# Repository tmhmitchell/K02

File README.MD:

**Less, but better.** - Dieter Rams

After seeing the [Ferris Sweep](https://github.com/davidphilipbarr/Sweep) for the first time I've fallen in love, but as a designer I cannot accept the things the way they are. So I've done some experimentation with it.

I changed the overall form of the board so it can be a little bit more compact and be a canvas for expression in the matter of case design

This is a parcial redesign of the [Ferris Sweep 2 half-swept](https://github.com/davidphilipbarr/Sweep). In other words this is a:

- 34 keys.
- Diodeless.
- Low profile.
- Non-hotswap.
- Reversible PCB.
- Column staggered.
- [Tenting puck](https://splitkb.com/products/tenting-puck) compatible.
- Wireless and wired capable.
- Choc MBK spaced (17,5mm x 16,5mm).
- Cheaper than the [cheapino](https://github.com/tompi/cheapino) (at the time of the build).

### What have been done:

- Change PCB overall form.
- Add support screw holes.
- Add teardrop on solder joints.
- Reposition of the reset and power switch.
- Do an extensive and compreensive [assembly manual](/other/manuals/k02-assembly-manual.pdf).
- Create an alternative version with `USB-C` instead of `TRRS`.
- Add commissioned art by the brazilian artist [Aline Dal Pont](https://www.instagram.com/manifesto.efemero/).
- Remove all the informative silk graphics for a better looking board.

### What I may do<sup>1</sup>:

- Change the `USB-C` location.
- Make it compatible with choc V2 switches.
- Change the `USB-C` connector to mid-mount 6p.
- Design some _minimalist_ and _low profile_ cases.
- Create an 36 keys pcb with breakpoints/mousebites.
- Add a variation with choc spacing for [CFX keycaps](https://kbd.news/CFX-keycap-1553.html) (16,5mm x 16,5mm).

> <sup>1</sup> The main reason for not doing this at the moment is the lack of financial motivation. As I have to pay for every prototype and take time off to do the development and iterations I have to be mindful of the tasks I take. If you want to help [contact me](https://www.reddit.com/user/kynikoi_/) :)

## Versions

At the moment this repo contains 2 versions, one with `TRRS` and one with `USB-C` connecting the halves. The `TRRS` connector are objectively worse than the `USB-C` for this use case, due to it introducing a risk of short in the case that the halves are unpluged with the board powered on. On the other side, the `USB-C` if not wired correctly may introduce a [risk of being connected directly to a power supply](https://docs.qmk.fm/features/split_keyboard) by mistake. I've done the bare minimum to prevent it, I wired the `GND` and `VCC` trying to follow the USB protocol. Another problem with the `USB-C` is that this implementation doesn't follow the USB protocol, it just hijack some of the data pins.

The [gerber files are in the release section.](https://github.com/anothermimich/K02/releases)
The list of materials for each version are inside of the respective folder, [USB-C](/USB-C/README.MD) and [TRRS](/TRRS/README.MD).

## Assembly

As the pcb doesn't have any information guiding the assembly, I have done an [manual with visual instructions](/other/manuals/k02-assembly-manual.pdf).

## Keymap

I'm using the [Miryoku ZMK](https://github.com/manna-harbour/miryoku_zmk) keymap made by [Manna Harbour](https://github.com/manna-harbour). Bellow you can see the layout that I ended up<sup>2</sup>, if you want to replicate it you can use [compiled firmware](/other/keymaps/) or compile it from scratch with this [github workflow](https://github.com/anothermimich/miryoku_zmk/blob/master/.github/workflows/workflow-build-k02.yml), [custom_config.h](https://github.com/anothermimich/miryoku_zmk/blob/master/miryoku/custom_config.h), [cradio_left.conf](https://github.com/anothermimich/miryoku_zmk/blob/master/config/cradio_left.conf) and [cradio_right.conf](https://github.com/anothermimich/miryoku_zmk/blob/master/config/cradio_right.conf) files.

> <sup>2</sup> I'm waiting miryoku support for `.svg` export or for the maintanner to send me the files to generate it manually. [More info can be found here](https://github.com/manna-harbour/miryoku/issues/72)

## Silk art

I commissioned the work of the brazilian artist [Aline Dal Pont](https://www.instagram.com/manifesto.efemero/) for this board. You can use it as it is (with the credits) for non-commercial ends. You cannot use the work outside of this board, modify it in any way or use it commercially without the express autorization of the artist.

## Firmware

As this redesign had only touched on aesthetic aspects, you can use the firmware from the [Ferris Sweep](https://github.com/davidphilipbarr/Sweep).

## Disclaimer

The files in this repo may contain problems, use them at your own risk.

For the type nerds _(like me)_, the text on the PCB and logo are [FuturaRenner](https://www.fontsquirrel.com/fonts/futura-renner) aka [Formera](https://github.com/noirblancrouge/Formera).

The team behind the design of the incredible [Ferris Sweep](https://github.com/davidphilipbarr/Sweep) are: [Pierre Chevalier](https://github.com/pierrechevalier83), [David Barr](https://github.com/davidphilipbarr), [Ibnu Daru Aji](https://github.com/ibnuda/), [Duccio](https://github.com/duckyb). Without their work this parcial redesign would not be possible.

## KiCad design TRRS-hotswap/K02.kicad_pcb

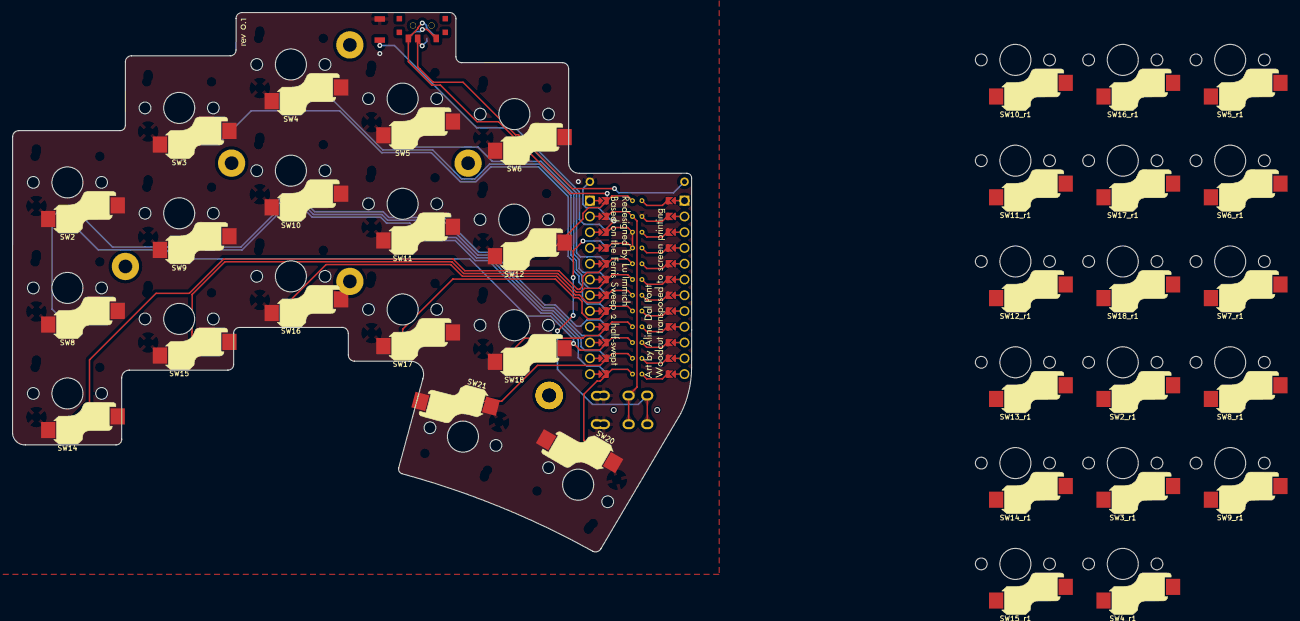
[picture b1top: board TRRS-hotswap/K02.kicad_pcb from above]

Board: 2 copper layers, 109.4 x 86.9 mm, 40 parts (0 on the bottom side), 23 nets.

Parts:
Bat+r1: MountingHole_Pad; 1pin_conn
BatGND1: MountingHole_Pad; 1pin_conn
J2: AudioJack4dpb; TRRS-PJ-DPB2
POWER SW: SW_SPDT; SPDT_C128955
RSW2: SW_Push; Tactile-Switch_SMT
SW2, SW2_r1, SW3, SW3_r1, SW4, SW4_r1, SW5, SW5_r1, SW6, SW6_r1, SW7_r1, SW8, SW8_r1, SW9, SW9_r1, SW10, SW10_r1, SW11, SW11_r1, SW12, SW12_r1, SW13_r1, SW14, SW14_r1, SW15, SW15_r1, SW16, SW16_r1, SW17, SW17_r1, SW18, SW18_r1, SW20, SW21: SW_Push; keyswitch_choc12_hotswap_1u
U1: ProMicro-kbd; ProMicro_jumpers_facedown

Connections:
BT+_r: Bat+r1.1, POWER SW.2
Switch1: SW2.1, U1.10
Switch2: SW3.1, U1.17
Switch3: SW4.1, U1.18
Switch4: SW5.1, U1.19
Switch5: SW6.1, U1.20
Switch6: SW8.1, U1.16
Switch7: SW9.1, U1.15
Switch8: SW10.1, U1.14
Switch9: SW11.1, U1.13
Switch10: SW12.1, U1.1
Switch11: SW14.1, U1.5
Switch12: SW15.1, U1.6
Switch13: SW16.1, U1.7
Switch14: SW17.1, U1.8
Switch15: SW18.1, U1.9
Switch16: SW20.1, U1.11
Switch17: SW21.1, U1.12
Switch18: J2.R1, U1.2
gnd: BatGND1.1, J2.S, J2.T, RSW2.1, RSW2.2, SW2.2, SW2_r1.2, SW3.2, SW3_r1.2, SW4.2, SW4_r1.2, SW5.2, SW5_r1.2, SW6.2, SW6_r1.2, SW7_r1.2, SW8.2, SW8_r1.2, SW9.2, SW9_r1.2, SW10.2, SW10_r1.2, SW11.2, SW11_r1.2, SW12.2, SW12_r1.2, SW13_r1.2, SW14.2, SW14_r1.2, SW15.2, SW15_r1.2, SW16.2, SW16_r1.2, SW17.2, SW17_r1.2, SW18.2, SW18_r1.2, SW20.2, SW21.2, U1.3, U1.4, U1.23
raw: POWER SW.3, U1.24
reset: RSW2.1, RSW2.2, U1.22
vcc: J2.R2, U1.21

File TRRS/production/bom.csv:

Designator,Footprint,Quantity,Value,LCSC Part #
"_3, _2, ",,3,,
"B+, B-",1pin_conn,2,MountingHole_Pad,
J2,TRRS-PJ-DPB2,1,AudioJack4dpb,
POWER SW,SPDT_C128955,1,SW_SPDT,
RSW2,Tactile-Switch_SMT,1,SW_Push,
"SW1, SW10, SW11, SW12, SW13, SW14, SW15, SW16, SW17, SW2, SW3, SW4, SW5, SW6, SW7, SW8, SW9",SW_PG1350_rev_DPB,17,SW_Push,
U1,ProMicro_jumpers_facedown,1,ProMicro-kbd,

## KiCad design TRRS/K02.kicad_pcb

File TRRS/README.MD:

# Necessary Components

| Quantity | What                                                                                                                              |
| -------- | --------------------------------------------------------------------------------------------------------------------------------- |
| 2        | Controller ([nrf52840 or pro micro compatible](https://github.com/joric/nrfmicro/wiki/Alternatives))                              |
| 34       | Switches ([Kailh PG1350/choc V1](https://cdn-shop.adafruit.com/product-files/5113/CHOC+keyswitch_Kailh-CPG135001D01_C400229.pdf)) |
| 34       | Keycaps choc v1 spaced ([MBK](https://fkcaps.com/keycaps/mbk) are the ideal size)                                                 |
| 2        | Reset switches (Omron [B3U-1000P(M)](https://omronfs.omron.com/en_US/ecb/products/pdf/en-b3u.pdf))                                |
| 4        | Header ([12pin](https://github.com/joric/nrfmicro/wiki/Sockets))                                                                  |
| ?        | Rubber feet (8mm x 2mm)                                                                                                           |

## Wireless

| What | Quantity                        |
| ---- | ------------------------------- |
| 2    | Power switches (MSK 12C02)      |
| 2    | Lithium battery (301230 110mah) |

## Wired

| What | Quantity                                         |
| ---- | ------------------------------------------------ |
| 1    | USB Cable (depends on the micro-controller used) |
| 2    | TRRS jack (PJ-320A)                              |
| 1    | TRRS cable                                       |

# PCB

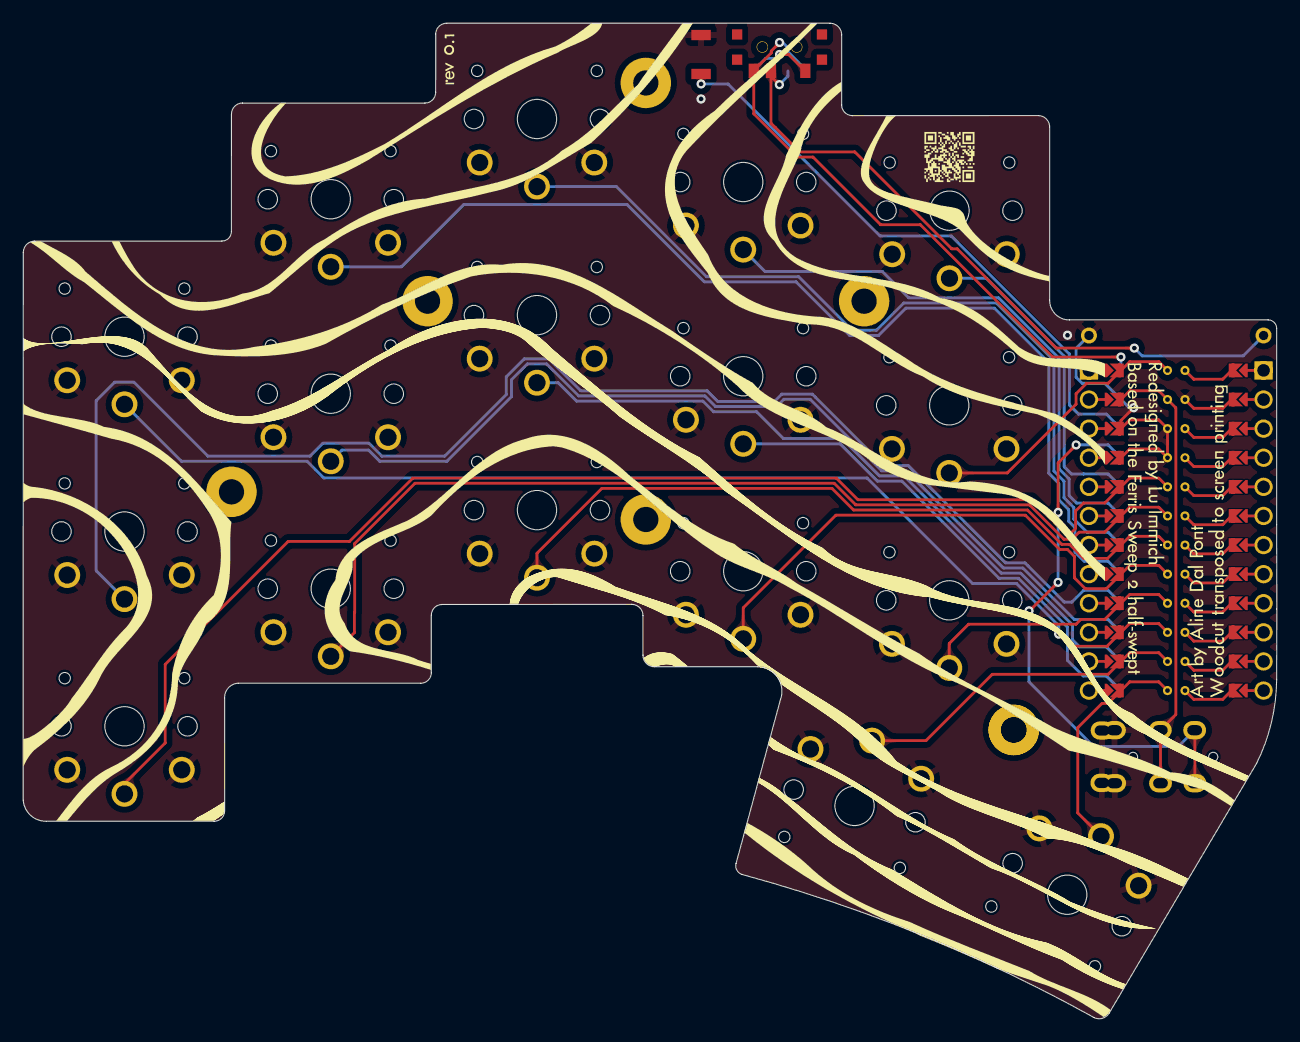
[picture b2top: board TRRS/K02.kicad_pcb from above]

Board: 2 copper layers, 109.4 x 86.9 mm, 23 parts (0 on the bottom side), 23 nets.

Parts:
B+: MountingHole_Pad; 1pin_conn
B-: MountingHole_Pad; 1pin_conn
J2: AudioJack4dpb; TRRS-PJ-DPB2
POWER SW: SW_SPDT; SPDT_C128955
RSW2: SW_Push; Tactile-Switch_SMT
SW1, SW2, SW3, SW4, SW5, SW6, SW7, SW8, SW9, SW10, SW11, SW12, SW13, SW14, SW15, SW16, SW17: SW_Push; SW_PG1350_rev_DPB
U1: ProMicro-kbd; ProMicro_jumpers_facedown

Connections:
BT+_r: B+.1, POWER SW.2
Switch1: SW1.1, U1.10
Switch2: SW2.1, U1.17
Switch3: SW3.1, U1.18
Switch4: SW4.1, U1.19
Switch5: SW5.1, U1.20
Switch6: SW6.1, U1.16
Switch7: SW7.1, U1.15
Switch8: SW8.1, U1.14
Switch9: SW9.1, U1.13
Switch10: SW10.1, U1.1
Switch11: SW11.1, U1.5
Switch12: SW12.1, U1.6
Switch13: SW13.1, U1.7
Switch14: SW14.1, U1.8
Switch15: SW15.1, U1.9
Switch16: SW16.1, U1.11
Switch17: SW17.1, U1.12
Switch18: J2.R1, U1.2
gnd: B-.1, J2.S, J2.T, RSW2.1, RSW2.2, SW1.2, SW2.2, SW3.2, SW4.2, SW5.2, SW6.2, SW7.2, SW8.2, SW9.2, SW10.2, SW11.2, SW12.2, SW13.2, SW14.2, SW15.2, SW16.2, SW17.2, U1.3, U1.4, U1.23
raw: POWER SW.3, U1.24
reset: RSW2.1, RSW2.2, U1.22
vcc: J2.R2, U1.21

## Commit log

2024-11-08 hallo
2024-11-08 board
2024-11-08 auuuu
2024-11-08 olar
2024-11-09 new changes
2024-11-09 new version
2024-11-14 new new new
2024-11-14 add img
2024-11-14 que?
2024-11-15 change in name sistem
2024-11-15 agr vai
2024-11-16 last
2024-11-16 with gerbers
2024-11-16 end??
2024-11-16 kiki
2024-11-16 gitignore
2024-11-16 .gitignore
2024-11-16 file change
2024-11-16 lalala
2024-11-16 done
2024-11-16 added case
2024-11-16 better credits
2024-11-16 choc update
2024-11-17 fix on the rights
2024-11-17 citation
2024-11-17 updated spacing
2024-11-18 case update
2024-11-18 opsi
2024-11-19 kerf update
2024-11-19 ready
2024-11-19 README
2024-11-19 link
2024-11-22 the case is ready
2024-11-22 readyyyy
2024-11-22 uhull
2024-11-22 now with magnets
2024-11-22 measurements
2024-11-26 fixed
2024-11-26 new info
2024-11-26 something
2024-11-26 opsss
2024-11-26 new files
2024-12-03 added manual
2024-12-03 remove title
2024-12-03 wrong shade of white
2024-12-05 parts update
2024-12-05 readme link and delete redundant files
2024-12-06 rubber feet amount
2024-12-08 imgs
2024-12-08 float center
2024-12-08 upsie
2024-12-08 aesthetic
2024-12-08 change aspect ratio
2024-12-08 banner
2024-12-08 no banner
2024-12-08 iiii
2024-12-08 keymap info
2024-12-09 pro micro alternative reference
2024-12-09 contact
2024-12-09 reorg
2024-12-09 Update LICENSE
2024-12-15 license info made clear
2024-12-15 border radius
2024-12-15 float
2024-12-15 img size
2024-12-15 iteste
2024-12-16 header info and link to parts
2024-12-16 photos
2024-12-16 clarification
2024-12-16 sintax
2024-12-16 regenerate gerber
2024-12-17 somewhat done
2024-12-17 new rodemap objectives
2024-12-18 finally the miryoku are done
2024-12-18 firmware with debounce right and with zmk sleep
2025-01-19 Begin work on hotswap version
